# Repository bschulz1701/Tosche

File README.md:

# Tosche
A collection of power converters for development and desktop use

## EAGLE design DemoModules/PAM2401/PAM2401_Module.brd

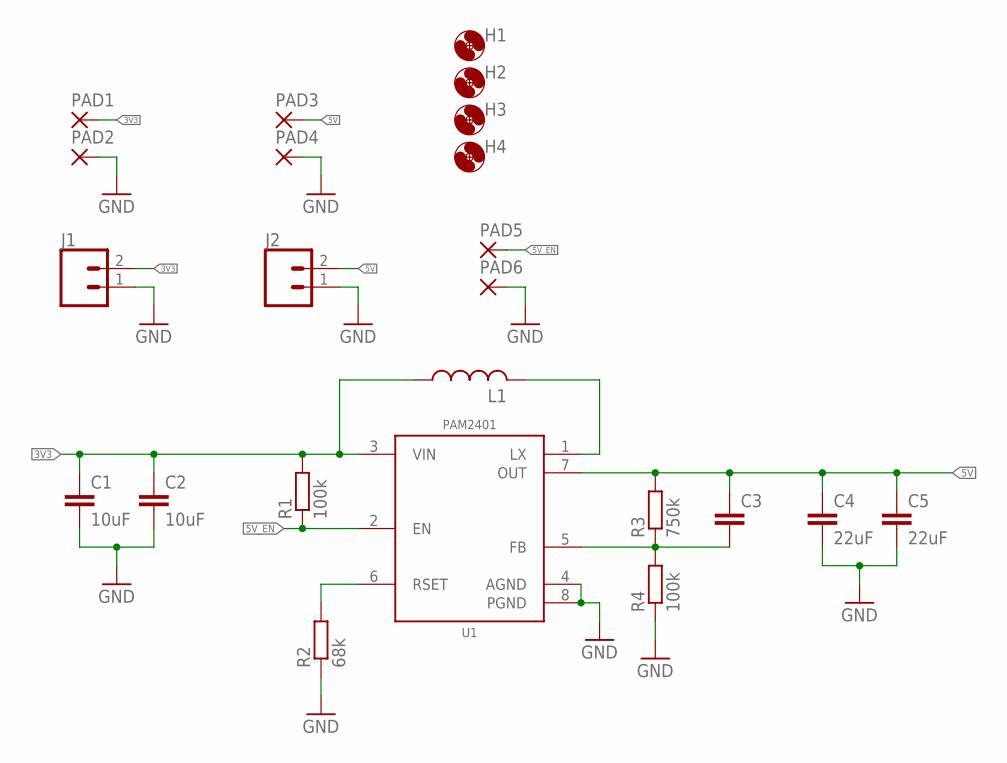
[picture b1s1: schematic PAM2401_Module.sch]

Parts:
C1, C2: 10uF; C0805
C3: C-EUC0603; C0603
C4, C5: 22uF; C0805
H1, H2, H3, H4: MOUNTING_HOLE2_NP; 2_56
J1, J2: CONN_023.5MM_ROUND_RESTRICT; SCREWTERMINAL-3.5MM-2_ROUND_RESTRICT
L1: INDUCTOR_MAPI_2.5X2; WE-MAPI(2.5X2)
PAD1, PAD2, PAD3, PAD4: SMD5; SMD2,54-5,08
PAD5, PAD6: SMD2; SMD1,27-2,54
R1, R4: 100k; R0603
R2: 68k; R0603
R3: 750k; R0603
U1: PAM2401MSOP; MSOP_8

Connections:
3V3: C1.1, C2.1, J1.2, L1.P$1 (1), PAD1.1, R1.2, U1.3 (VIN)
5V: C3.1, C4.1, C5.1, J2.2, PAD3.1, R3.2, U1.7 (OUT)
5V_EN: PAD5.1, R1.1, U1.2 (EN)
GND: C1.2, C2.2, C4.2, C5.2, J1.1, J2.1, PAD2.1, PAD4.1, PAD6.1, R2.1, R4.1, U1.4 (AGND), U1.8 (PGND)
unnamed: R2.2, U1.6 (RSET)
unnamed: C3.2, R3.1, R4.2, U1.5 (FB)
unnamed: L1.P$2 (2), U1.1 (LX)

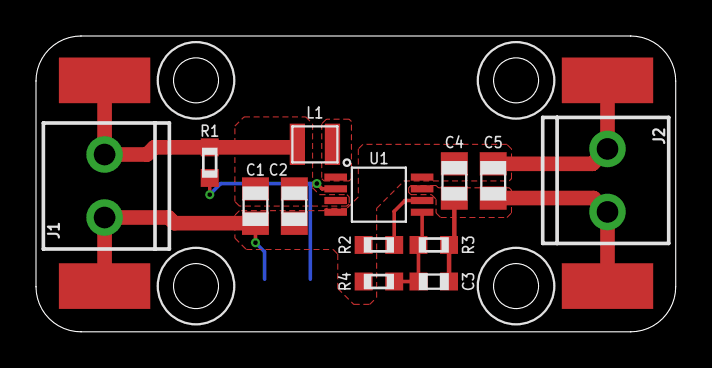
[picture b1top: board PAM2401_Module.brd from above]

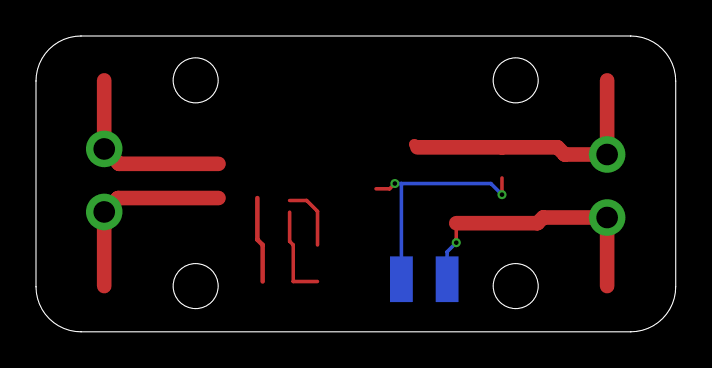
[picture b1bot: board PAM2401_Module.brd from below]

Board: 2 copper layers, 35.5 x 16.4 mm, 23 parts (2 on the bottom side), 7 nets.

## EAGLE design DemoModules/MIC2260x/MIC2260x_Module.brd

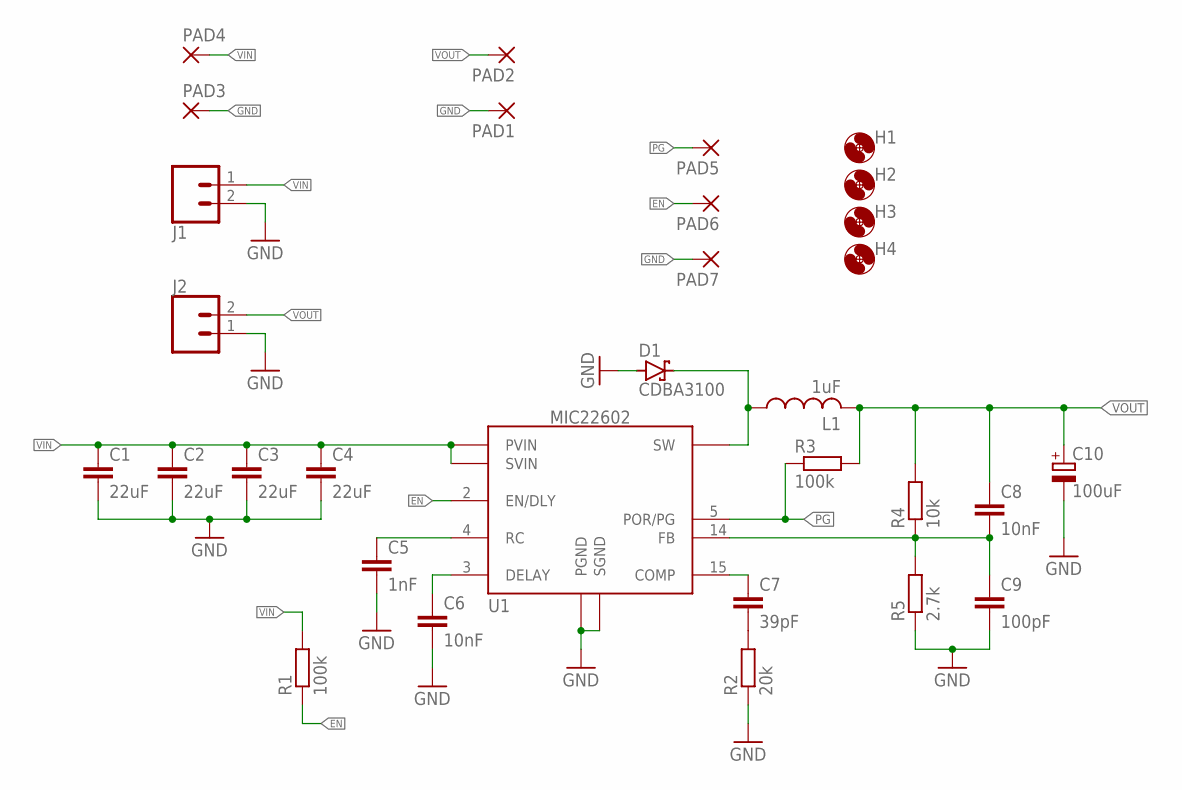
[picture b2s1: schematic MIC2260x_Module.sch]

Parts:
C1, C2, C3, C4: 22uF; C0805
C5: 1nF; C0402
C6, C8: 10nF; C0402
C7: 39pF; C0402
C9: 100pF; C0402
C10: 100uF; C1411_TANT
D1: CDBA3100; DO214AC
H1, H2, H3, H4: MOUNTING_HOLE4_NP; 4_40
J1, J2: CONN_023.5MM_ROUND_RESTRICT; SCREWTERMINAL-3.5MM-2_ROUND_RESTRICT
L1: 1uF; WE-MAIA(4.1X4.1)
PAD1, PAD2, PAD3, PAD4: SMD5; SMD2,54-5,08
PAD5, PAD6, PAD7: SMD2; SMD1,27-2,54
R1, R3: 100k; R0402
R2: 20k; R0402
R4: 10k; R0402
R5: 2.7k; R0402
U1: MIC22602; QFN24_POWER

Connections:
COMP: C7.1, U1.15 (COMP)
DELAY: C6.1, U1.3 (DELAY)
EN: PAD6.1, R1.1, U1.2 (EN/DLY)
FB: C8.2, C9.1, R4.1, R5.2, U1.14 (FB)
GND: C1.2, C2.2, C3.2, C4.2, C5.2, C6.2, C9.2, C10.CATHODE (-), D1.A, J1.2, J2.1, PAD1.1, PAD3.1, PAD7.1, R2.1, R5.1, U1.7 (PGND), U1.12 (PGND), U1.16 (SGND), U1.19 (PGND), U1.24 (PGND), U1.EP (PGND), U1.EP@1 (PGND), U1.EP@2 (PGND), U1.EP@3 (PGND), U1.EP@4 (PGND), U1.EP@5 (PGND), U1.EP@6 (PGND), U1.EP@7 (PGND), U1.EP@8 (PGND), U1.EP@9 (PGND)
unnamed: C7.2, R2.2
PG: PAD5.1, R3.1, U1.5 (POR/PG)
RC: C5.1, U1.4 (RC)
SW: D1.C, L1.P$1 (1), U1.8 (SW), U1.9 (SW), U1.10 (SW), U1.11 (SW), U1.20 (SW), U1.21 (SW), U1.22 (SW), U1.23 (SW)
VIN: C1.1, C2.1, C3.1, C4.1, J1.1, PAD4.1, R1.2, U1.1 (PVIN), U1.6 (PVIN), U1.13 (PVIN), U1.17 (SVIN), U1.18 (PVIN)
VOUT: C8.1, C10.ANODE (+), J2.2, L1.P$2 (2), PAD2.1, R3.2, R4.2

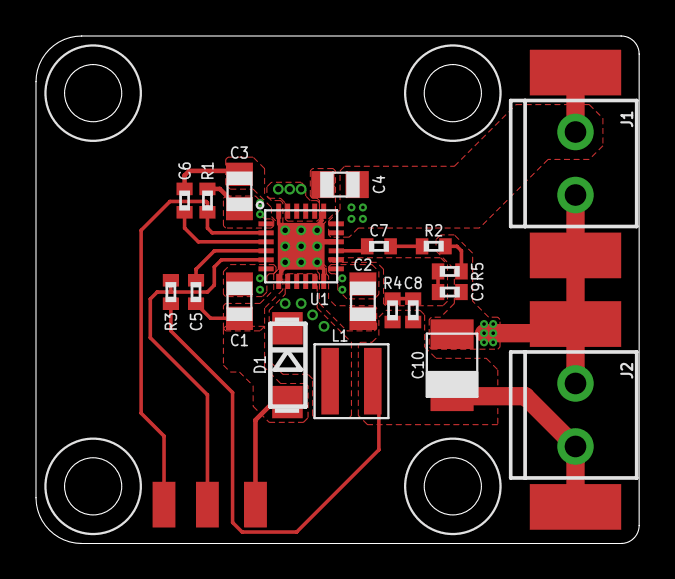
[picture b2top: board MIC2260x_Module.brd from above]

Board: 2 copper layers, 33.5 x 28.2 mm, 31 parts (0 on the bottom side), 11 nets.

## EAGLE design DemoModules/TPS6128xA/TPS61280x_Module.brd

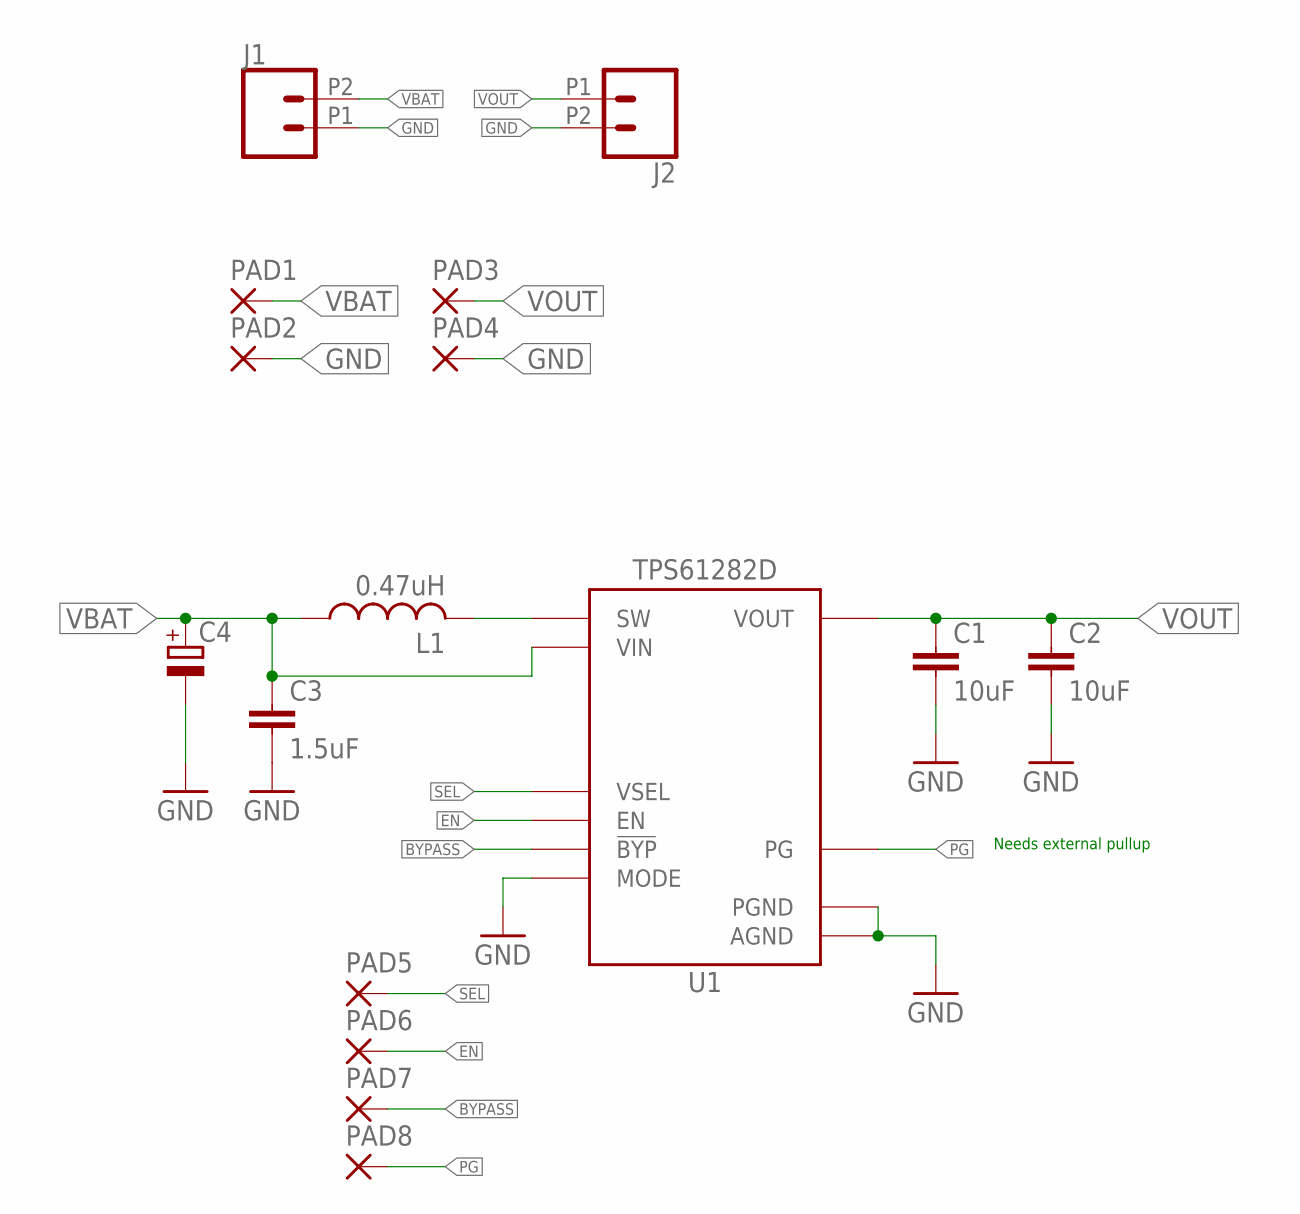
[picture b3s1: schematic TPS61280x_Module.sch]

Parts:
C1, C2: 10uF; C0805
C3: 1.5uF; C0805
C4: CTANT_EU2917; C2917
J1, J2: CONN_022.54_SCREW_ROUND; 1X02_2.54_SCREWTERM_ROUND
L1: 0.47uH; WE-MAPI(4.1X4.1)
PAD1, PAD2, PAD3, PAD4: SMD5; SMD2,54-5,08
PAD5, PAD6, PAD7, PAD8: SMD2; SMD1,27-2,54
U1: TPS61282D; YFP0016

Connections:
BYPASS: PAD7.1, U1.C1 (!BYP)
EN: PAD6.1, U1.A1 (EN)
GND: C1.2, C2.2, C3.2, C4.-, J1.P1 (1), J2.P2 (2), PAD2.1, PAD4.1, U1.B2 (MODE), U1.C2 (AGND), U1.D1 (AGND), U1.D2 (PGND), U1.D3 (PGND), U1.D4 (PGND)
PG: PAD8.1, U1.A2 (PG)
SEL: PAD5.1, U1.B1 (VSEL)
SW: L1.P$2 (2), U1.C3 (SW), U1.C4 (SW)
VBAT: C3.1, C4.+, J1.P2 (2), L1.P$1 (1), PAD1.1, U1.A3 (VIN), U1.A4 (VIN)
VOUT: C1.1, C2.1, J2.P1 (1), PAD3.1, U1.B3 (VOUT), U1.B4 (VOUT)

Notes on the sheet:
Needs external pullup

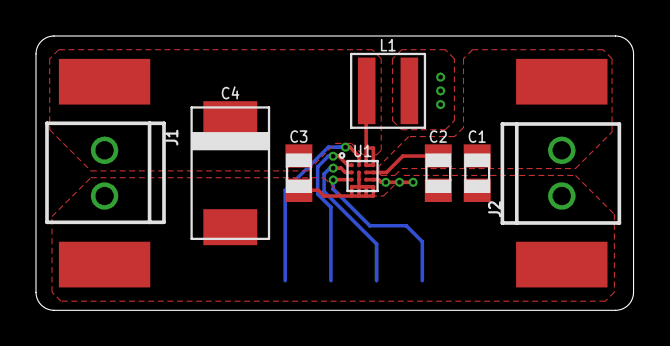
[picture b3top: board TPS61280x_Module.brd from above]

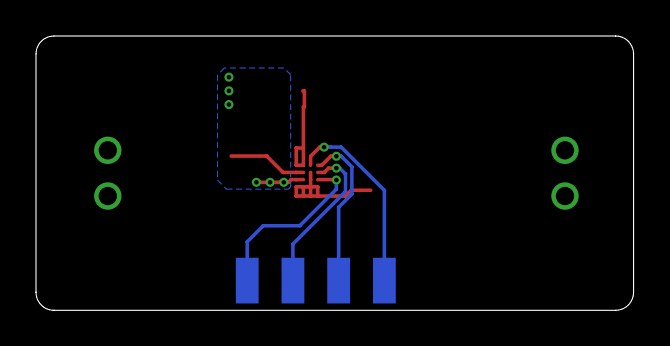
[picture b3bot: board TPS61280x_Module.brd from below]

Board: 2 copper layers, 33.2 x 15.2 mm, 16 parts (4 on the bottom side), 8 nets.

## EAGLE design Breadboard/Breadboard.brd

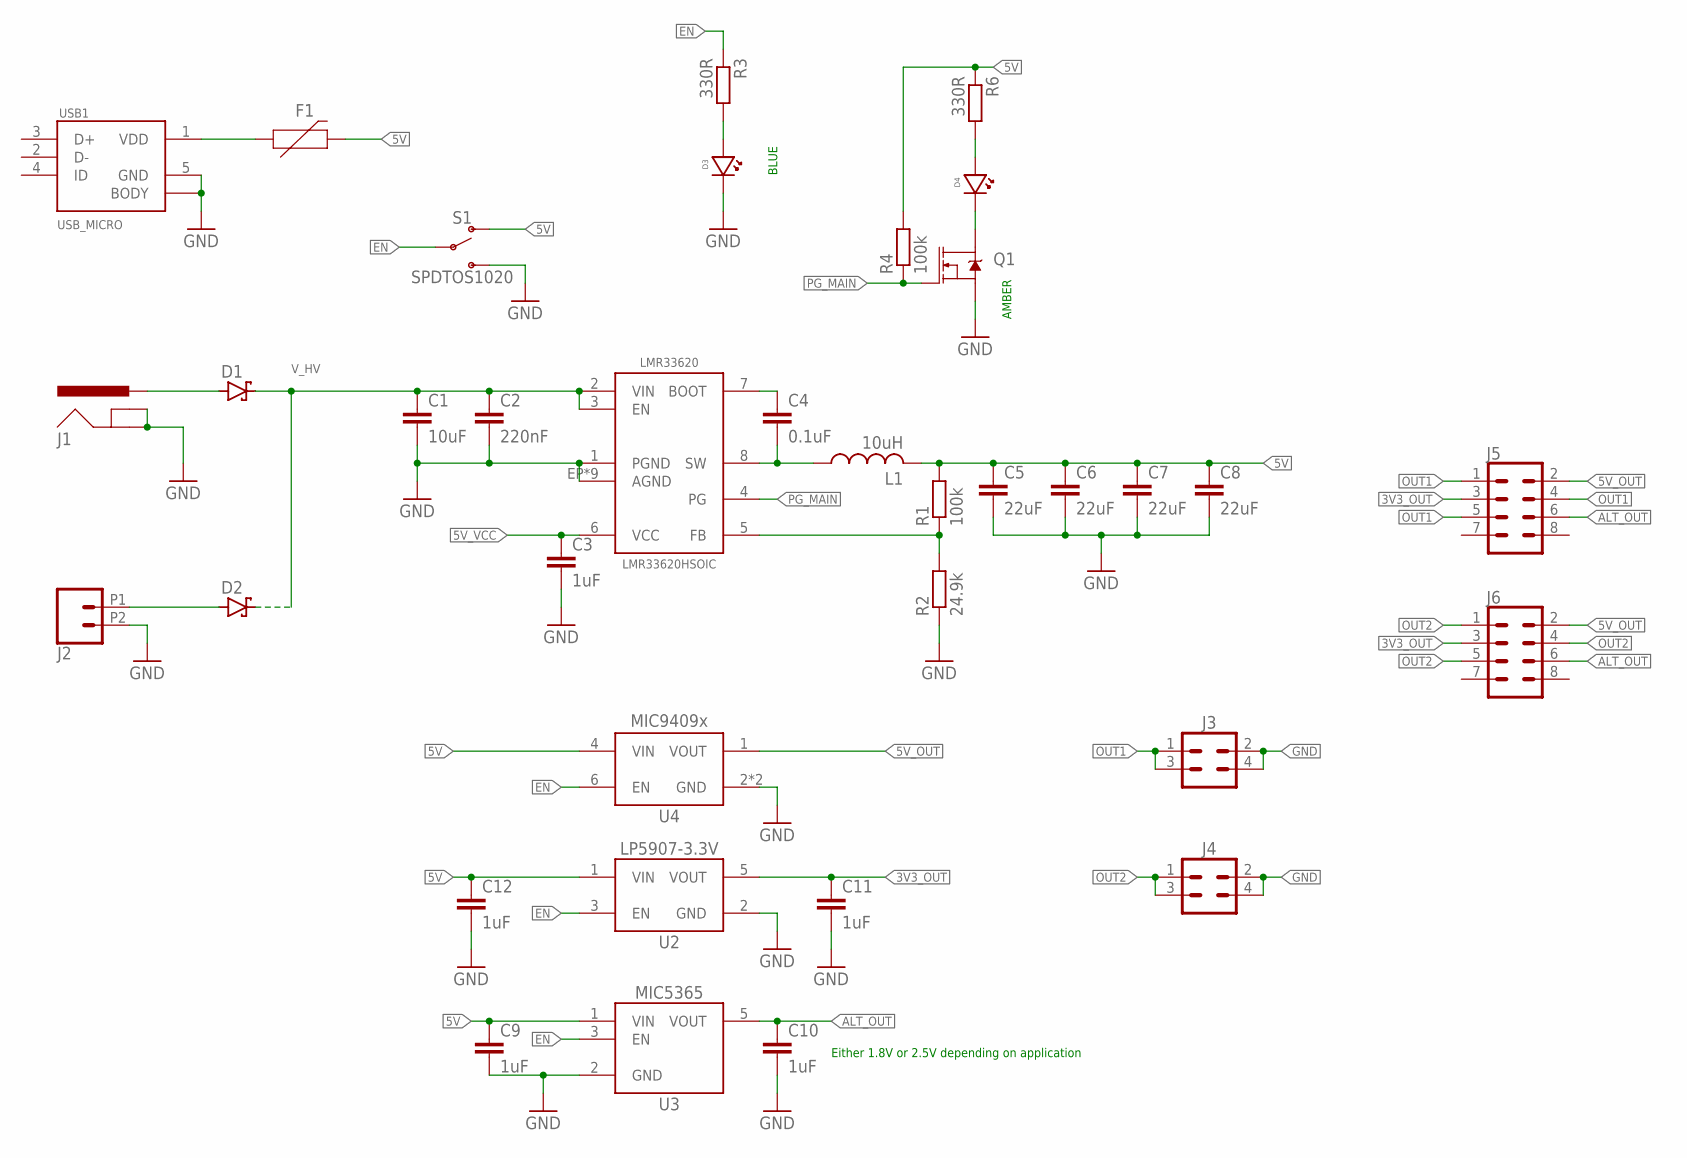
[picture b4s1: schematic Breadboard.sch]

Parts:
C1: 10uF; C0805
C2: 220nF; C0603
C3, C9, C10, C11, C12: 1uF; C0603
C4: 0.1uF; C0603
C5, C6, C7, C8: 22uF; C0805
D1, D2: DIODE_SCHOTTKYSOD-123; SOD-123
D3: LEDBLUE0603; LED_0603
D4: LEDAMBER0603; LED_0603
F1: PPTC_HALF-AMP; 1206
J1: POWER_JACKSLT; POWER_JACK_SLOT
J2: CONN_022.54_SCREW; 1X02_2.54_SCREWTERM
J3, J4: CONN_2X2; 2X02
J5, J6: CONN_04X2; 2X4
L1: 10uH; WE-LQS(5X5)
Q1: MOSFET-NCH-2N7002P; SOT23-3
R1, R4: 100k; R0603
R2: 24.9k; R0603
R3, R6: 330R; R0603
S1: SPDTOS1020; OS102011MS2QN1
U1: LMR33620HSOIC; DDS0008J
U2: LP59073.3VDBV; SOT23-5
U3: MIC53651.8SOT23; SOT23-5
U4: MIC9409C6; SC-70_6
USB1: USB_MICRO; 10118194-0001LF_10118194-0001LF_LONGER_PADS

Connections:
3V3_OUT: C11.1, J5.3, J6.3, U2.5 (VOUT)
5V: C5.1, C6.1, C7.1, C8.1, C9.1, C12.1, F1.2, L1.2, R1.2, R4.2, R6.1, S1.1 (O), U2.1 (VIN), U3.1 (VIN), U4.4 (VIN)
5V_OUT: J5.2, J6.2, U4.1 (VOUT)
5V_VCC: C3.1, U1.6 (VCC)
ALT_OUT: C10.1, J5.6, J6.6, U3.5 (VOUT)
EN: R3.1, S1.2, U2.3 (EN), U3.3 (EN), U4.6 (EN)
GND: C1.2, C2.2, C3.2, C5.2, C6.2, C7.2, C8.2, C9.2, C10.2, C11.2, C12.2, D3.CATHODE, J1.GND@1 (GNDBREAK), J1.GND@2 (GND), J2.P2 (2), J3.2, J3.4, J4.2, J4.4, Q1.2 (S), R2.1, S1.3 (S), U1.1 (PGND), U1.EP (AGND), U1.EP@1 (AGND), U1.EP@2 (AGND), U1.EP@3 (AGND), U1.EP@4 (AGND), U1.EP@5 (AGND), U1.EP@6 (AGND), U1.EP@7 (AGND), U1.EP@8 (AGND), U2.2 (GND), U3.2 (GND), U4.2 (GND), U4.5 (GND), USB1.5 (GND), USB1.BODY@1 (BODY), USB1.BODY@2 (BODY), USB1.BODY@3 (BODY), USB1.BODY@4 (BODY), USB1.BODY@7 (BODY), USB1.BODY@8 (BODY)
unnamed: R1.1, R2.2, U1.5 (FB)
unnamed: D1.ANODE (A), J1.PWR
unnamed: D2.ANODE (A), J2.P1 (1)
unnamed: F1.1, USB1.1 (VDD)
unnamed: C4.2, L1.1, U1.8 (SW)
unnamed: C4.1, U1.7 (BOOT)
unnamed: D4.CATHODE, Q1.3 (D)
unnamed: D3.ANODE, R3.2
unnamed: D4.ANODE, R6.2
OUT1: J3.1, J3.3, J5.1, J5.4, J5.5
OUT2: J4.1, J4.3, J6.1, J6.4, J6.5
PG_MAIN: Q1.1 (G), R4.1, U1.4 (PG)
V_HV: C1.1, C2.1, D1.CAT (C), D2.CAT (C), U1.2 (VIN), U1.3 (EN)

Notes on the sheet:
BLUE
AMBER
Either 1.8V or 2.5V depending on application

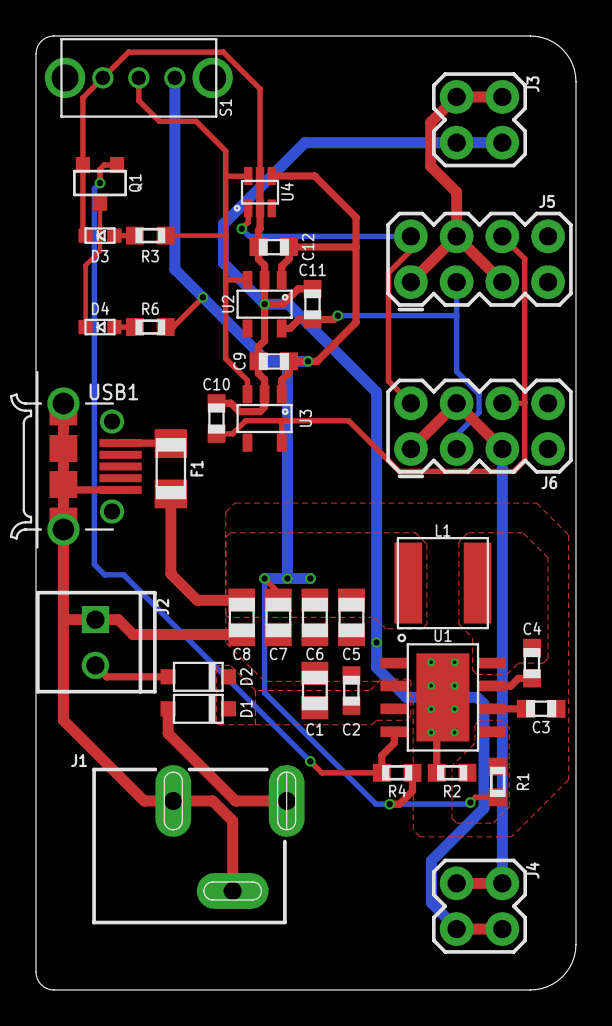
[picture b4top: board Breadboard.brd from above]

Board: 2 copper layers, 30.0 x 53.0 mm, 36 parts (0 on the bottom side), 20 nets.

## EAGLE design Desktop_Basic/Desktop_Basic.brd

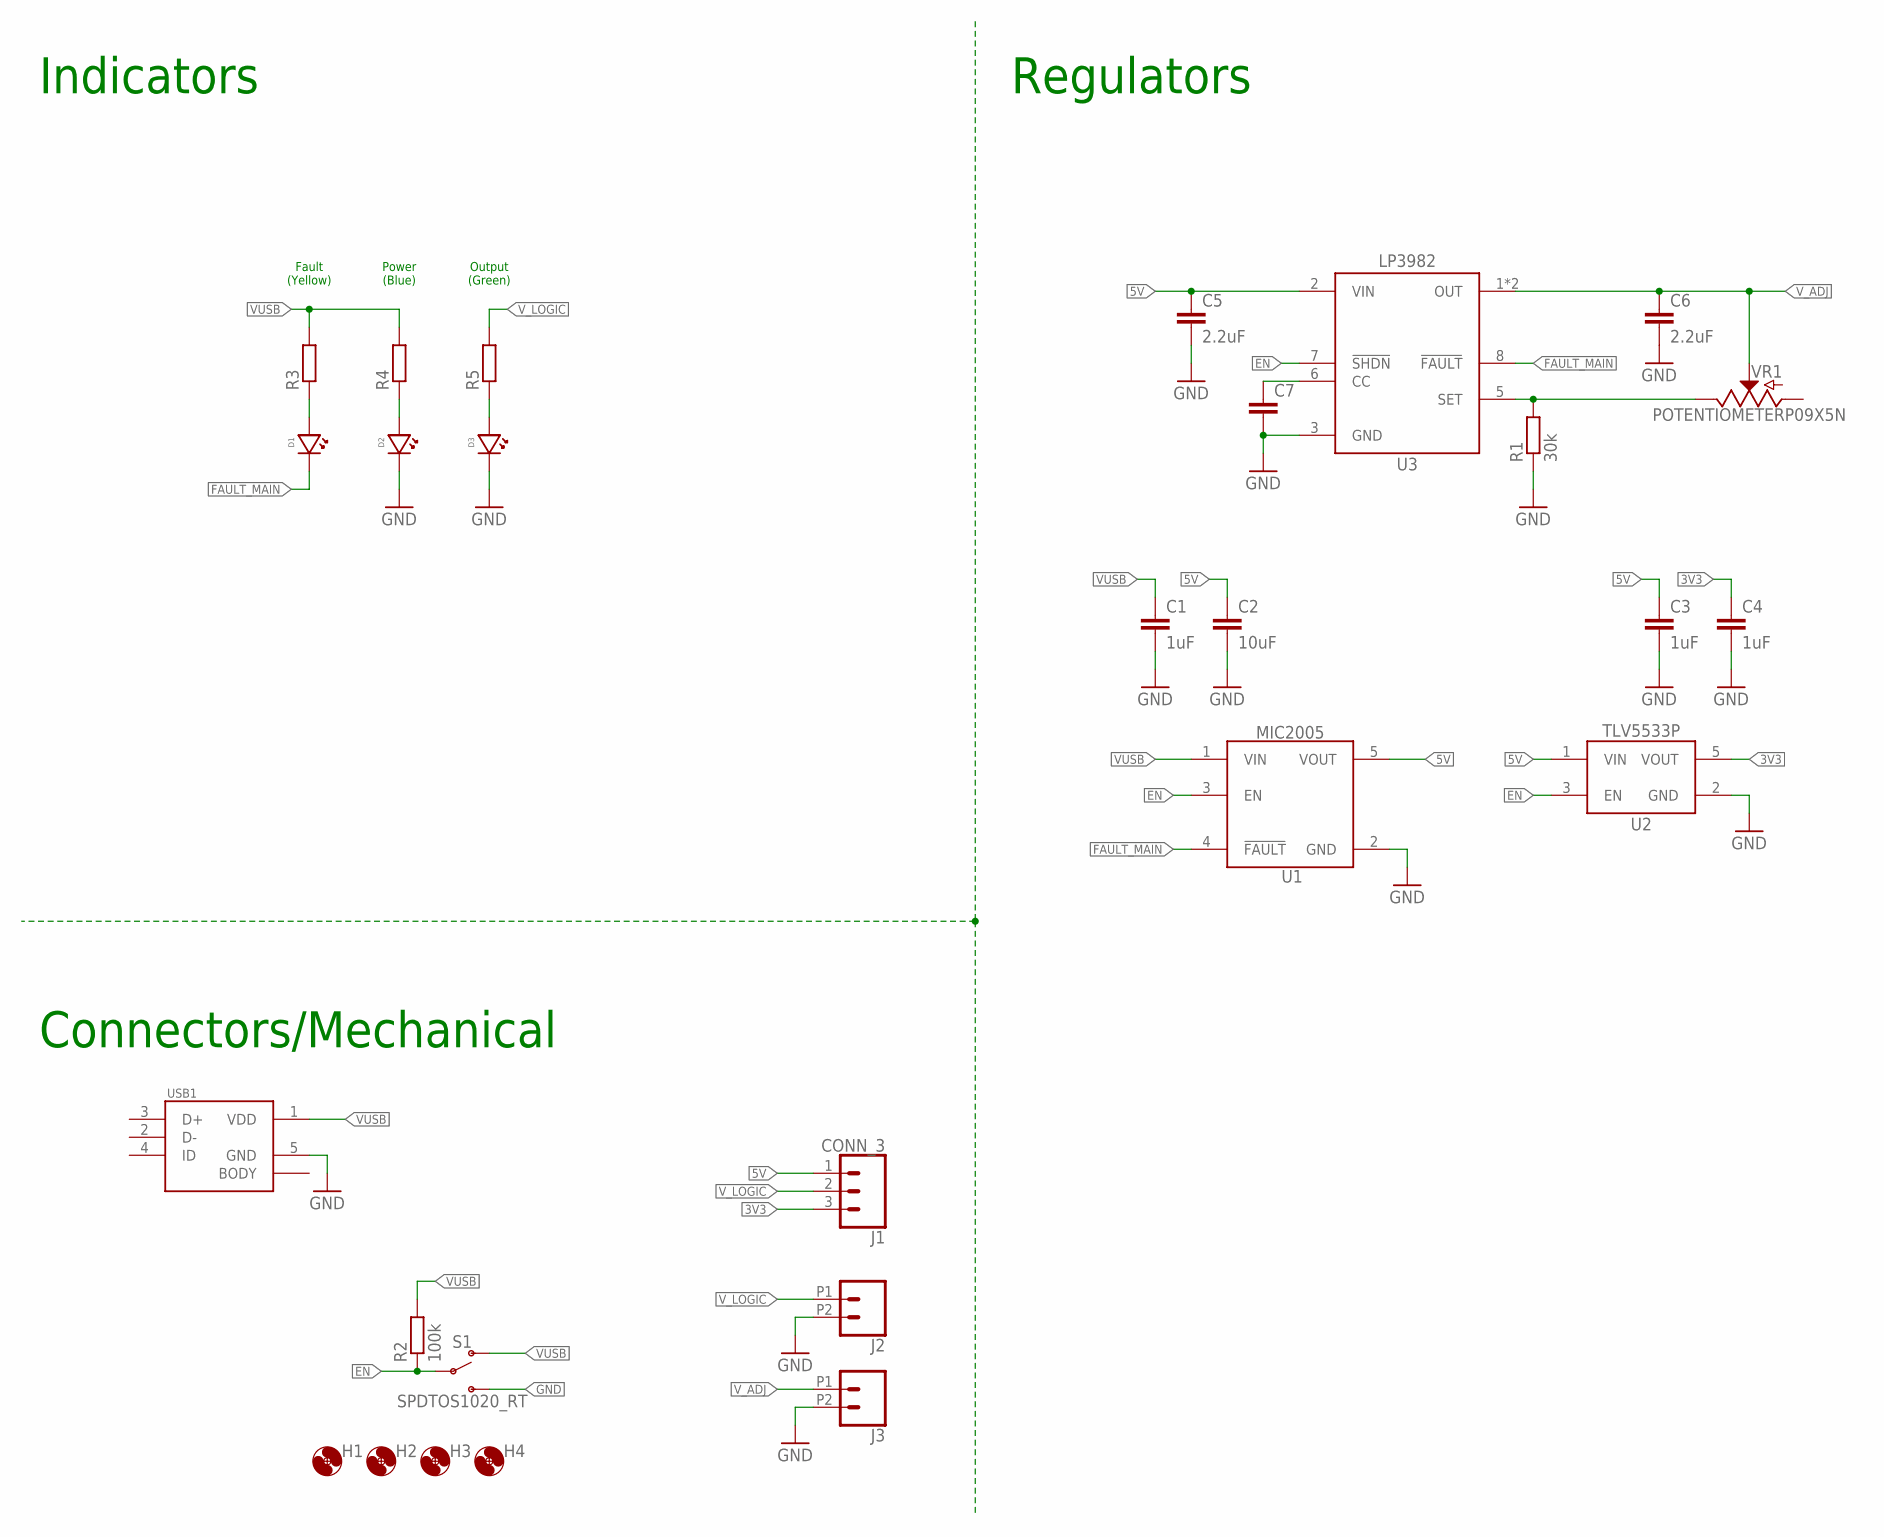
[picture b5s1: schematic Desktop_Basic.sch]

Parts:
C1, C3, C4: 1uF; C0603
C2: 10uF; C0805
C5, C6: 2.2uF; C0603
C7: C-EUC0603; C0603
D1: LED0603; LED_0603
D2: LEDBLUE0603; LED_0603
D3: LEDGREEN0603; LED_0603
H1, H2, H3, H4: MOUNTING_HOLE4_PL; 4_40_PLATED
J1: CONN_3; 1X03
J2, J3: CONN_022.54_SCREW_ROUND; 1X02_2.54_SCREWTERM_ROUND
R1: 30k; R0603
R2: 100k; R0603
R3, R4, R5: R-EU_330R0603; R0603
S1: SPDTOS1020_RT; OS102011MA1QN1
U1: MIC2005; SOT23-5
U2: TLV755P3V3SOT23; DBV0005A
U3: LP3982ADJVSSOP; DGK_S-PDSO-G8
USB1: MICRO_USB_LONGPADS; 10118194-0001LF_10118194-0001LF_LONGER_PADS
VR1: POTENTIOMETERP09X5N; P0915N

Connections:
3V3: C4.1, J1.3, U2.5 (VOUT)
5V: C2.1, C3.1, C5.1, J1.1, U1.5 (VOUT), U2.1 (VIN), U3.2 (VIN)
EN: R2.1, S1.2, U1.3 (EN), U2.3 (EN), U3.7 (!SHDN)
FAULT_MAIN: D1.CATHODE, U1.4 (!FAULT), U3.8 (!FAULT)
GND: C1.2, C2.2, C3.2, C4.2, C5.2, C6.2, C7.2, D2.CATHODE, D3.CATHODE, J2.P2 (2), J3.P2 (2), R1.1, S1.3 (S), U1.2 (GND), U2.2 (GND), U3.3 (GND), USB1.5 (GND)
unnamed: C7.1, U3.6 (CC)
unnamed: D1.ANODE, R3.1
unnamed: R1.2, U3.5 (SET), VR1.3 (E)
unnamed: D2.ANODE, R4.1
unnamed: D3.ANODE, R5.1
VUSB: C1.1, R2.2, R3.2, R4.2, S1.1 (O), U1.1 (VIN), USB1.1 (VDD)
V_ADJ: C6.1, J3.P1 (1), U3.1 (OUT), U3.4 (OUT), VR1.2 (S)
V_LOGIC: J1.2, J2.P1 (1), R5.2

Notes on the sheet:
Fault (Yellow)
Power (Blue)
Output (Green)
Connectors/Mechanical
Indicators
Regulators

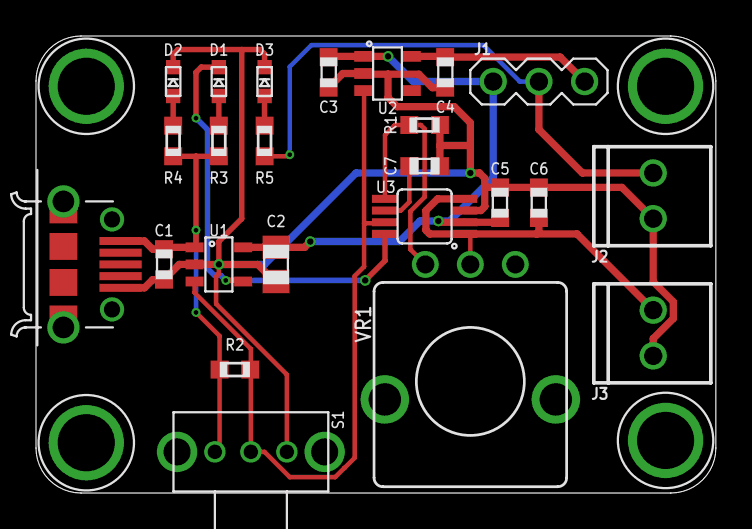
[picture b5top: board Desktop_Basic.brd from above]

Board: 2 copper layers, 37.8 x 25.4 mm, 28 parts (0 on the bottom side), 13 nets.

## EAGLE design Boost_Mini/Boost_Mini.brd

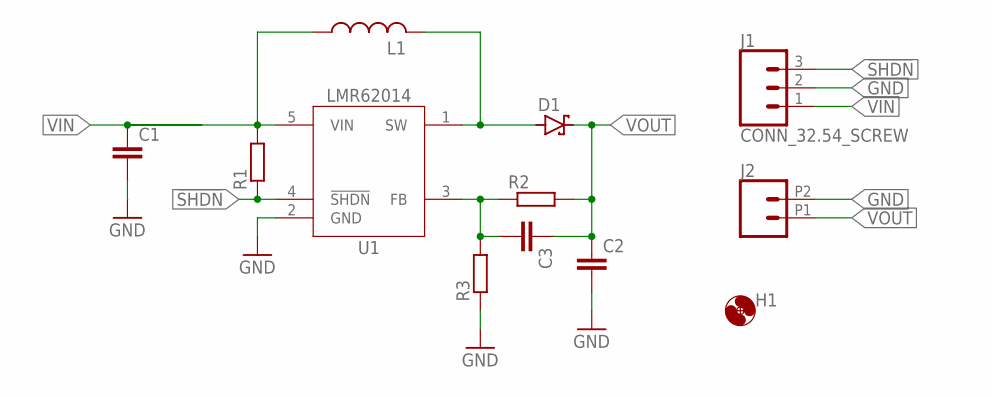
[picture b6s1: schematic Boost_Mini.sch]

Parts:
C1, C2: C-EUC0805; C0805
C3: C-EUC0603; C0603
D1: DIODE_SCHOTTKYDO-214AC; DO214AC
H1: MOUNTING_HOLE2_NP; 2_56
J1: CONN_32.54_SCREW; 1X03_SCREW
J2: CONN_022.54_SCREW_ROUND; 1X02_2.54_SCREWTERM_ROUND
L1: INDUCTORMAIA_4.1X4.1; WE-MAIA(4.1X4.1)
R1, R2, R3: R-EU_R0603; R0603
U1: LMR62014SOT23; DBV0005A

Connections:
!SHDN: J1.3, R1.1, U1.4 (!SHDN)
GND: C1.2, C2.2, J1.2, J2.P2 (2), R3.1, U1.2 (GND)
unnamed: C3.2, R2.1, R3.2, U1.3 (FB)
unnamed: D1.A, L1.P$2 (2), U1.1 (SW)
VIN: C1.1, J1.1, L1.P$1 (1), R1.2, U1.5 (VIN)
VOUT: C2.1, C3.1, D1.C, J2.P1 (1), R2.2

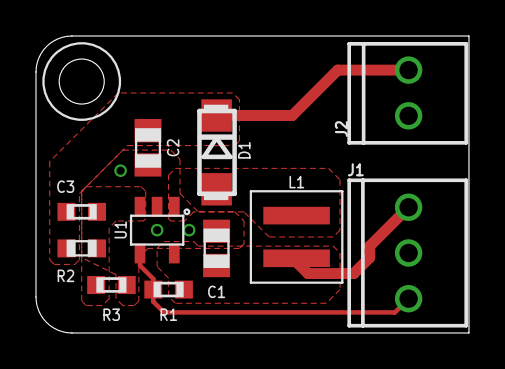
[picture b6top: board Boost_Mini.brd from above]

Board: 2 copper layers, 24.1 x 16.5 mm, 12 parts (0 on the bottom side), 6 nets.

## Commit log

2020-06-24 Added LICENSE
2020-06-24 Added initial dev of DesktopBasic and BoostMini
    Bulk addition of version v0.0 of DesktopBasic and BoostMini
2021-04-14 Development for Breadboard power supply
    Design and gerber generation for breadboard power supply, v0.0 sent to fab
2024-11-02 Updated modules

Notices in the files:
parts and their libraries:
bschulz: This work is licensed under the Creative Commons Attribution-ShareAlike 4.0
http://creativecommons.org/licenses/by-sa/4.0
